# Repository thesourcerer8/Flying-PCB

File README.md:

# Flying-PCB
Quadcopter Project by MCI &amp; Infineon

This is a Quadcopter software and harddware design created as an cooperation by MCI and Infineon.

More information about the project: http://copter.rocks/

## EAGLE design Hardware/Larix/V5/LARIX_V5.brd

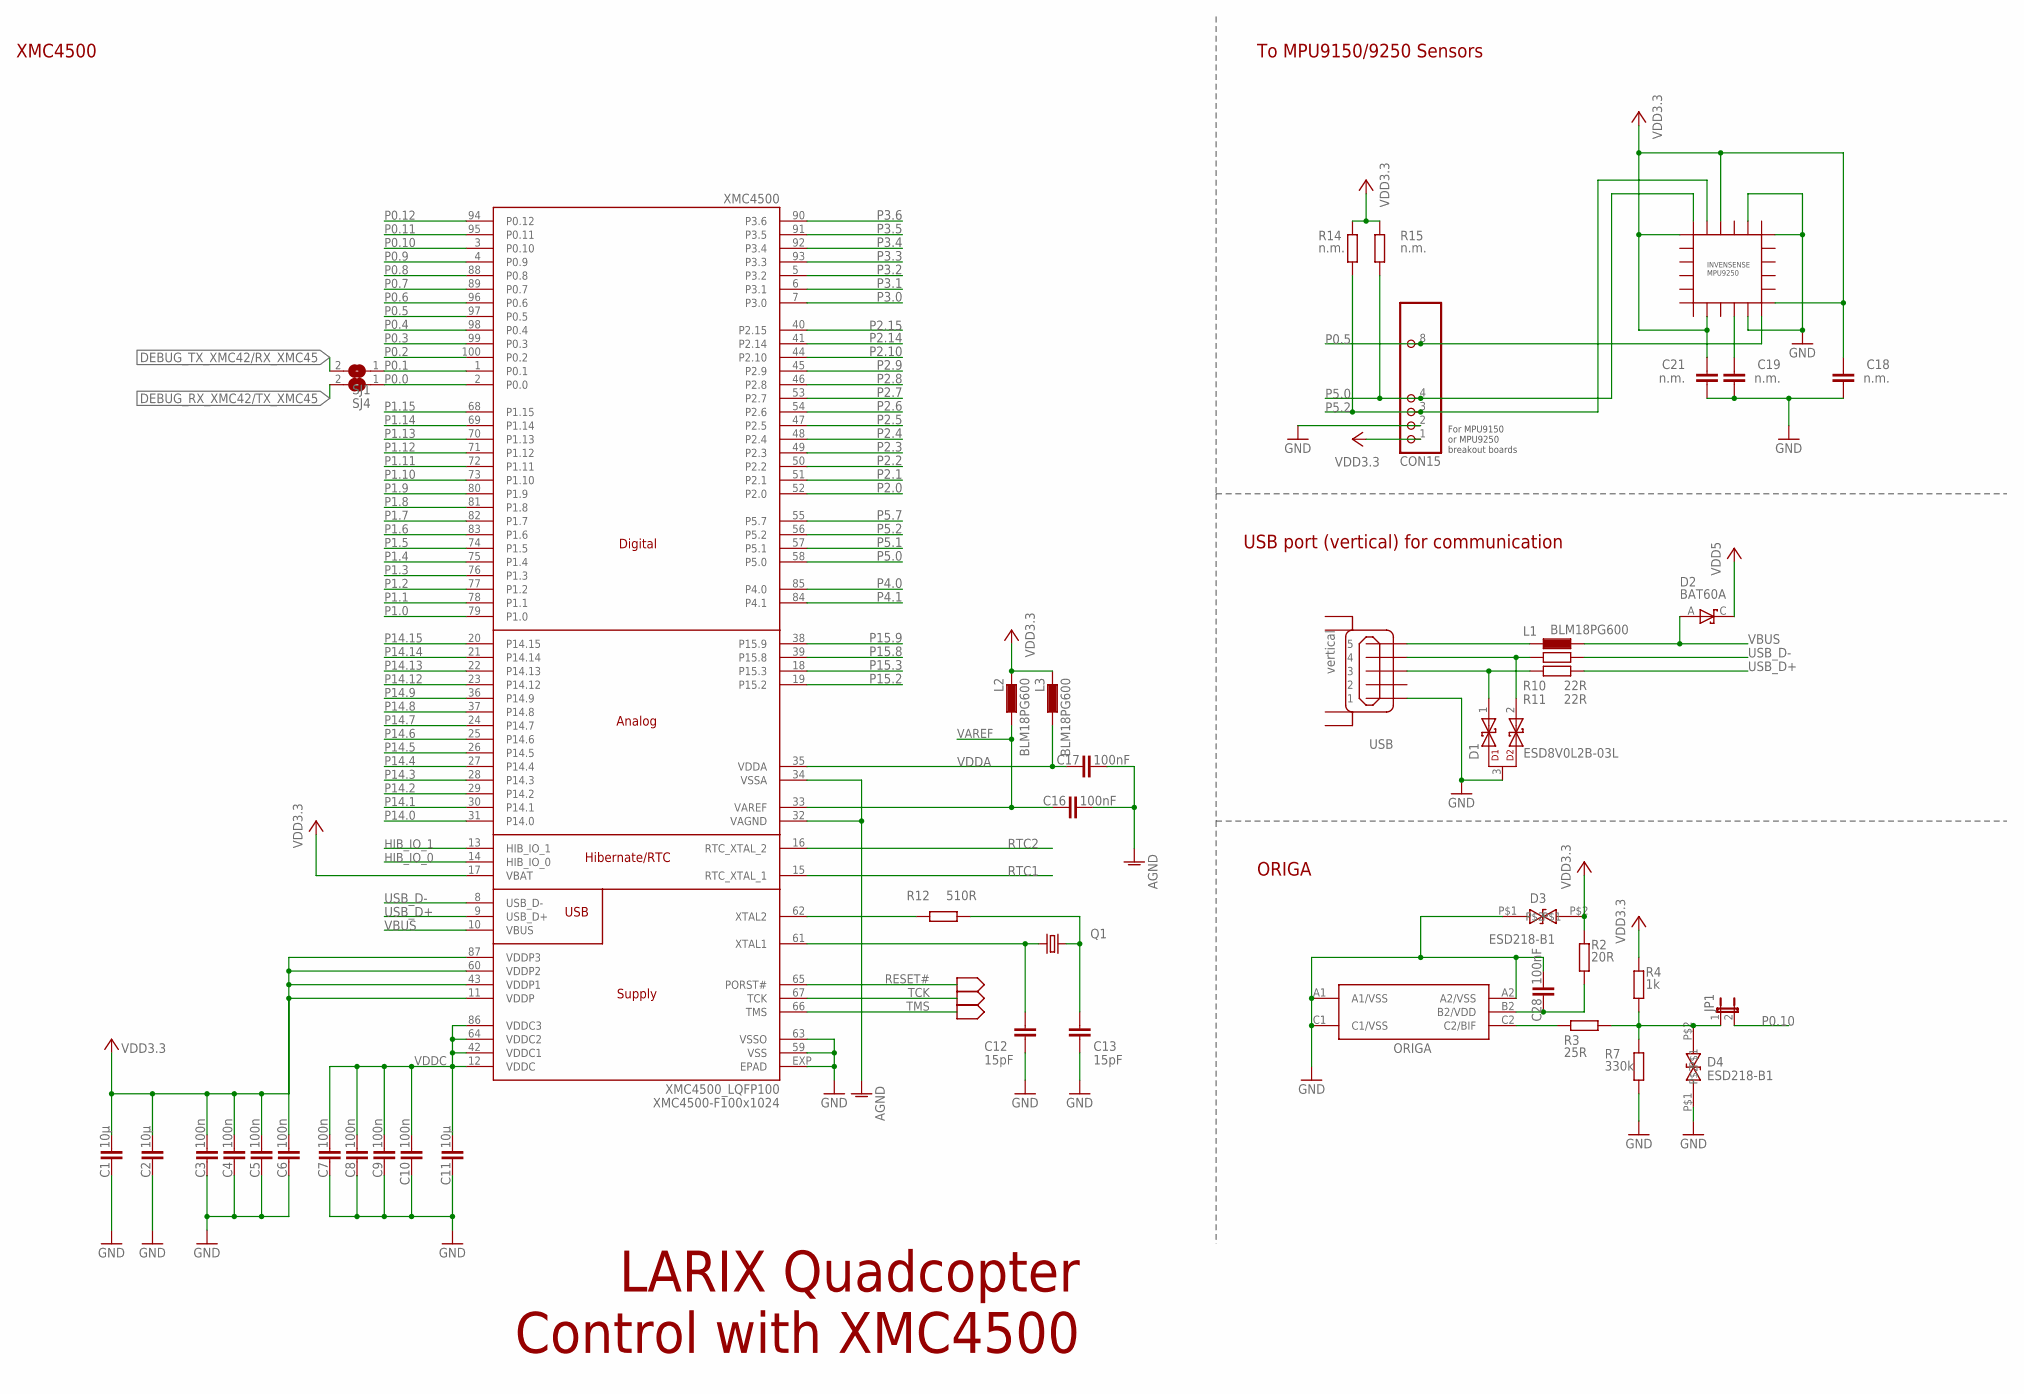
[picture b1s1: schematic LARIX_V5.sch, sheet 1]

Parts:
C1, C2, C11: 10µ; C0805K
C3, C4, C5, C6, C7, C8, C9, C10: 100n; C0603
C12, C13: 15pF; C0603
C16, C17, C28: 100nF; C0603
C18, C19, C21: n.m.; C0603
CON15: PINHD-1X10; 1X10
D1: ESD8V0L2B-03L; TSLP-3-1
D2: BAT60A; SOD323-R
D3, D4: ESD218-B1-02EL; TSLP-2-20
JP1: JP1E; JP1
L1, L2, L3: BLM18PG600; L1608
MPU9250: INVENSENSE9250EHERBY; QFN3X3-24+
ORIGA: ORIGA2L; WLB-5
Q1: 12MHZ/S/3.2X2.5; 32X25_4PAD
R2: 20R; R0603
R3: 25R; R0603
R4: 1k; R0603
R7: 330k; R0603
R10, R11: 22R; R0603
R12: 510R; R0603
R14, R15: n.m.; R0603
SJ1, SJ4: SJ
USB: vertical; USBVERTICAL
XMC4500: XMC4500_LQFP100; P/PG-LQFP-100-11

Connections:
AGND: C16.2, C17.2, XMC4500.32 (VAGND), XMC4500.34 (VSSA)
DEBUG_RX_XMC42/TX_XMC45: SJ4.2; also elsewhere on the board
DEBUG_TX_XMC42/RX_XMC45: SJ1.2; also elsewhere on the board
GND: C1.2, C2.2, C3.2, C4.2, C5.2, C6.2, C7.2, C8.2, C9.2, C10.2, C11.2, C12.2, C13.2, C18.1, C19.1, C21.1, C28.1, CON15.2, D1.3, D3.P$1, D4.P$1, MPU9250.11, MPU9250.18, MPU9250.20, ORIGA.A1 (A1/VSS), ORIGA.A2 (A2/VSS), ORIGA.C1 (C1/VSS), R7.2, USB.1, XMC4500.59 (VSS), XMC4500.63 (VSSO), XMC4500.EXP (EPAD); also elsewhere on the board
HIB_IO_0: XMC4500.14 (HIB_IO_0)
HIB_IO_1: XMC4500.13 (HIB_IO_1)
unnamed: C28.2, ORIGA.B2 (B2/VDD), R2.2
unnamed: R12.1, XMC4500.62 (XTAL2)
unnamed: C13.1, Q1.3 (2), R12.2
unnamed: C12.1, Q1.1, XMC4500.61 (XTAL1)
unnamed: D4.P$2, JP1.1, R3.2, R4.2, R7.1
unnamed: L1.2, USB.5
unnamed: ORIGA.C2 (C2/BIF), R3.1
unnamed: D1.2, R10.1, USB.4
unnamed: C19.2, MPU9250.10
unnamed: D1.1, R11.1, USB.3+ (3)
P0.0: SJ4.1, XMC4500.2 (P0.0); also elsewhere on the board
P0.1: SJ1.1, XMC4500.1 (P0.1); also elsewhere on the board
P0.2: XMC4500.100 (P0.2); also elsewhere on the board
P0.3: XMC4500.99 (P0.3); also elsewhere on the board
P0.4: XMC4500.98 (P0.4); also elsewhere on the board
P0.5: CON15.8, MPU9250.12, XMC4500.97 (P0.5)
P0.6: XMC4500.96 (P0.6)
P0.7: XMC4500.89 (P0.7); also elsewhere on the board
P0.8: XMC4500.88 (P0.8)
P0.9: XMC4500.4 (P0.9); also elsewhere on the board
P0.10: JP1.2, XMC4500.3 (P0.10)
P0.11: XMC4500.95 (P0.11)
P0.12: XMC4500.94 (P0.12)
P1.0: XMC4500.79 (P1.0); also elsewhere on the board
P1.1: XMC4500.78 (P1.1); also elsewhere on the board
P1.2: XMC4500.77 (P1.2); also elsewhere on the board
P1.3: XMC4500.76 (P1.3); also elsewhere on the board
P1.4: XMC4500.75 (P1.4)
P1.5: XMC4500.74 (P1.5); also elsewhere on the board
P1.6: XMC4500.83 (P1.6)
P1.7: XMC4500.82 (P1.7)
P1.8: XMC4500.81 (P1.8)
P1.9: XMC4500.80 (P1.9)
P1.10: XMC4500.73 (P1.10)
P1.11: XMC4500.72 (P1.11)
P1.12: XMC4500.71 (P1.12)
P1.13: XMC4500.70 (P1.13)
P1.14: XMC4500.69 (P1.14)
P1.15: XMC4500.68 (P1.15); also elsewhere on the board
P2.0: XMC4500.52 (P2.0)
P2.1: XMC4500.51 (P2.1); also elsewhere on the board
P2.2: XMC4500.50 (P2.2); also elsewhere on the board
P2.3: XMC4500.49 (P2.3); also elsewhere on the board
P2.4: XMC4500.48 (P2.4); also elsewhere on the board
P2.5: XMC4500.47 (P2.5); also elsewhere on the board
P2.6: XMC4500.54 (P2.6)
P2.7: XMC4500.53 (P2.7)
P2.8: XMC4500.46 (P2.8)
P2.9: XMC4500.45 (P2.9)
P2.10: XMC4500.44 (P2.10)
P2.14: XMC4500.41 (P2.14)
P2.15: XMC4500.40 (P2.15)
P3.0: XMC4500.7 (P3.0); also elsewhere on the board
P3.1: XMC4500.6 (P3.1); also elsewhere on the board
P3.2: XMC4500.5 (P3.2); also elsewhere on the board
P3.3: XMC4500.93 (P3.3)
P3.4: XMC4500.92 (P3.4)
P3.5: XMC4500.91 (P3.5); also elsewhere on the board
P3.6: XMC4500.90 (P3.6)
P4.0: XMC4500.85 (P4.0); also elsewhere on the board
P4.1: XMC4500.84 (P4.1)
P5.0: CON15.4, MPU9250.24, R15.1, XMC4500.58 (P5.0)
P5.1: XMC4500.57 (P5.1); also elsewhere on the board
P5.2: CON15.3, MPU9250.23, R14.1, XMC4500.56 (P5.2)
P5.7: XMC4500.55 (P5.7)
P14.0: XMC4500.31 (P14.0)
P14.1: XMC4500.30 (P14.1)
P14.2: XMC4500.29 (P14.2)
P14.3: XMC4500.28 (P14.3)
P14.4: XMC4500.27 (P14.4)
P14.5: XMC4500.26 (P14.5); also elsewhere on the board
P14.6: XMC4500.25 (P14.6)
P14.7: XMC4500.24 (P14.7); also elsewhere on the board
P14.8: XMC4500.37 (P14.8); also elsewhere on the board
P14.9: XMC4500.36 (P14.9)
P14.12: XMC4500.23 (P14.12)
P14.13: XMC4500.22 (P14.13)
P14.14: XMC4500.21 (P14.14)
P14.15: XMC4500.20 (P14.15)
P15.2: XMC4500.19 (P15.2)
P15.3: XMC4500.18 (P15.3)
P15.8: XMC4500.39 (P15.8)
P15.9: XMC4500.38 (P15.9)
RESET#: XMC4500.65 (PORST#); also elsewhere on the board
RTC1: XMC4500.15 (RTC_XTAL_1)
RTC2: XMC4500.16 (RTC_XTAL_2)
TCK: XMC4500.67 (TCK); also elsewhere on the board
TMS: XMC4500.66 (TMS); also elsewhere on the board
USB_D+: R11.2, XMC4500.9 (USB_D+)
USB_D-: R10.2, XMC4500.8 (USB_D-)
VAREF: C16.1, L2.1, XMC4500.33 (VAREF)
VBUS: D2.A, L1.1, XMC4500.10 (VBUS)
VDD3.3: C1.1, C2.1, C3.1, C4.1, C5.1, C6.1, C18.2, C21.2, CON15.1, D3.P$2, L2.2, L3.2, MPU9250.1, MPU9250.8, MPU9250.13, MPU9250.22, R2.1, R4.1, R14.2, R15.2, XMC4500.11 (VDDP), XMC4500.17 (VBAT), XMC4500.43 (VDDP1), XMC4500.60 (VDDP2), XMC4500.87 (VDDP3); also elsewhere on the board
VDD5: D2.C; also elsewhere on the board
VDDA: C17.1, L3.1, XMC4500.35 (VDDA)
VDDC: C7.1, C8.1, C9.1, C10.1, C11.1, XMC4500.12 (VDDC), XMC4500.42 (VDDC1), XMC4500.64 (VDDC2), XMC4500.86 (VDDC3)

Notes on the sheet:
LARIX Quadcopter Control with XMC4500
XMC4500-F100x1024
To MPU9150/9250 Sensors
ORIGA
XMC4500
For MPU9150 or MPU9250 breakout boards
USB port (vertical) for communication
ESD218-B1

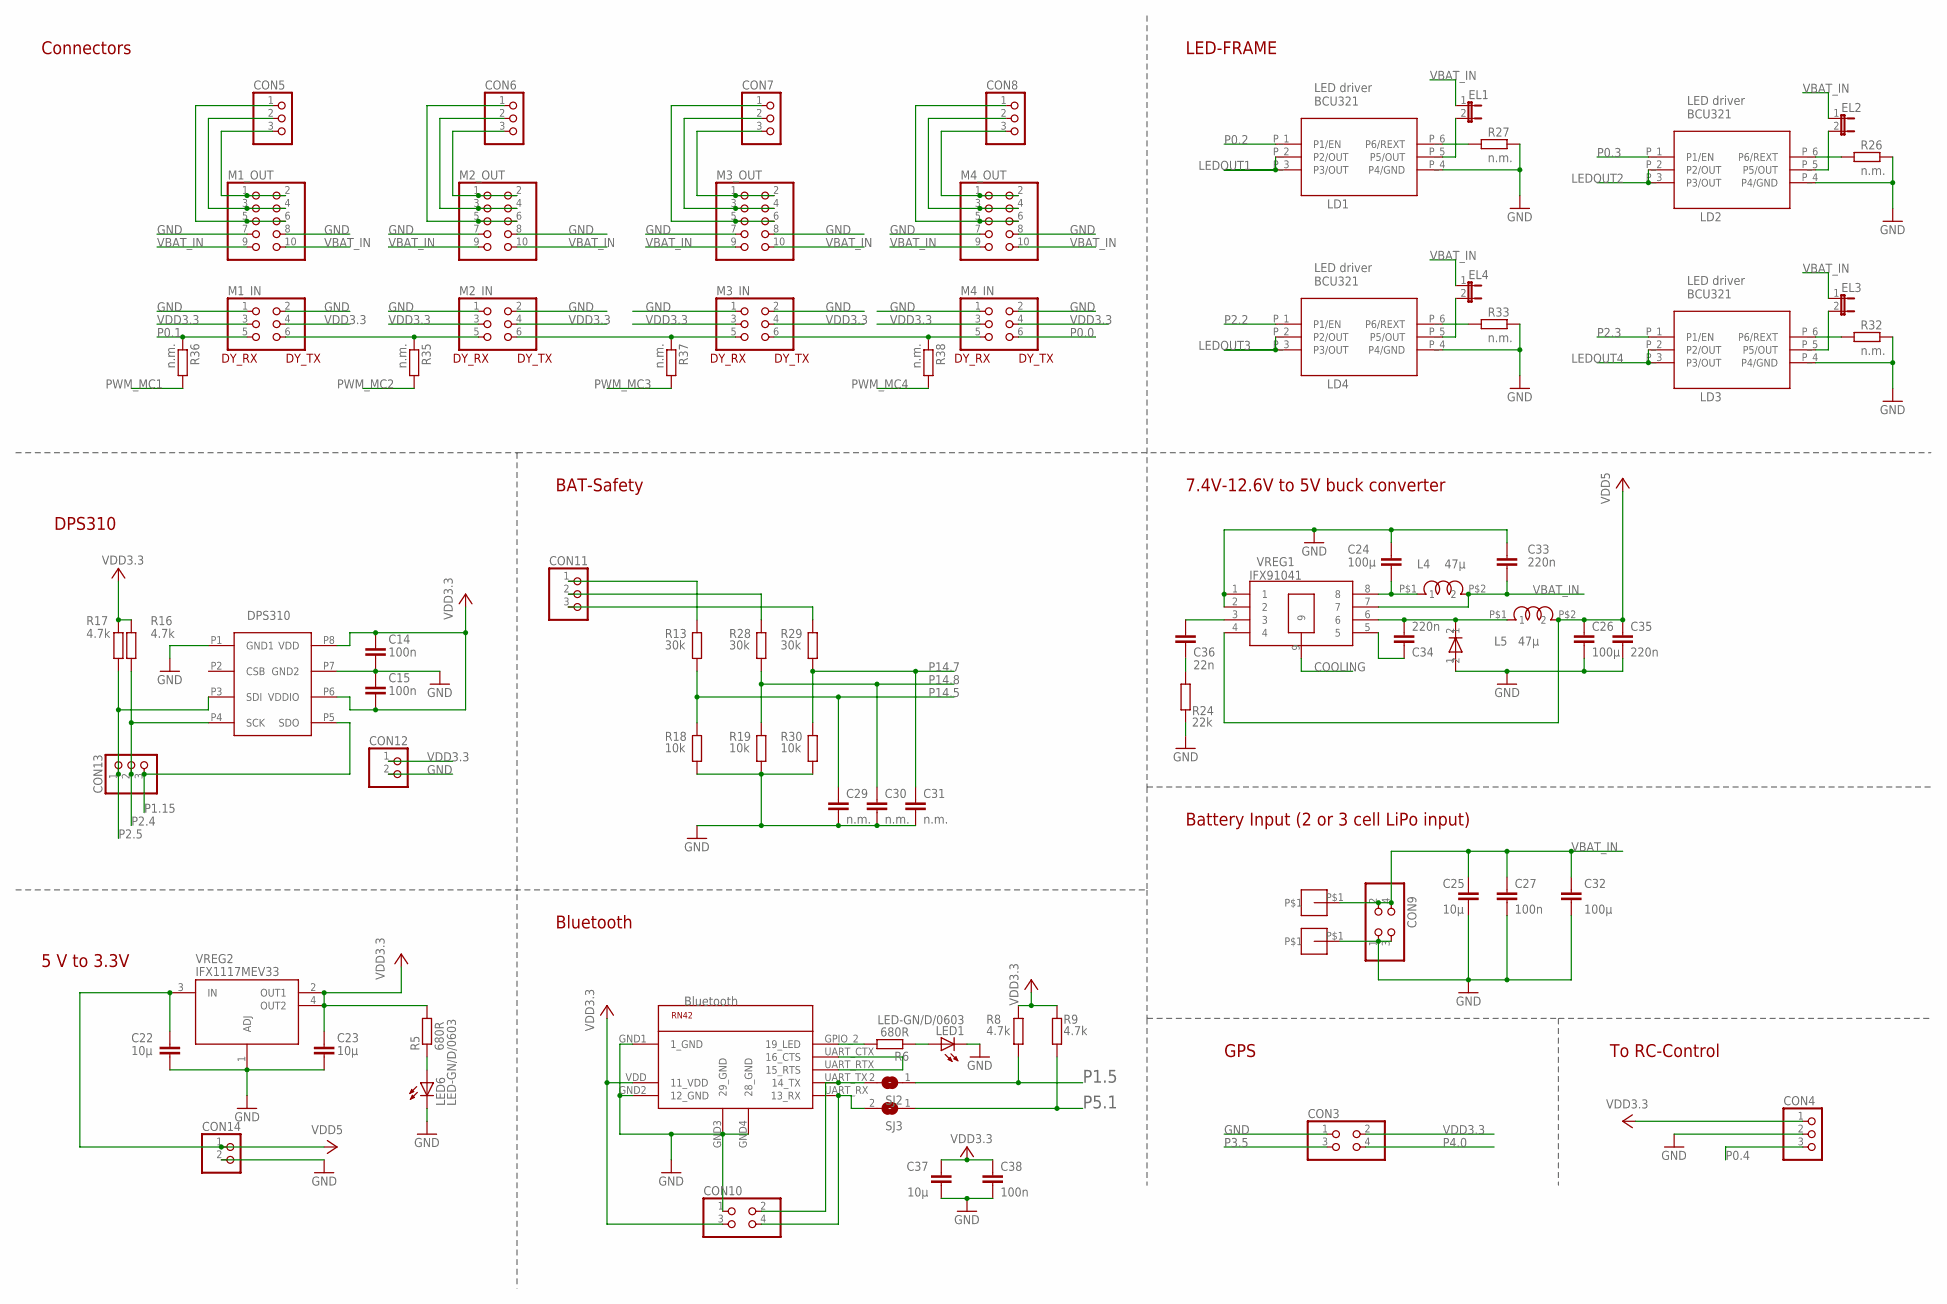
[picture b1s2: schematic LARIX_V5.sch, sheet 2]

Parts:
C14, C15, C27, C38: 100n; C0603
C22, C23, C25, C37: 10µ; C0805K
C24, C26, C32: 100µ; C1210
C29, C30, C31: n.m.; C0603
C33, C34, C35: 220n; C0603
C36: 22n; C0603
CON3, CON9, CON10: PINHD-2X2; 2X02
CON4, CON5, CON6, CON7, CON8, CON11, CON13: PINHD-1X3; 1X03
CON12, CON14: PINHD-1X2; 1X02
D6: BAS21-03W; INF-SOD323_V_1PRIMARY
DPS310: DPS310DRUCKSENSOR; LGA8R125P0X4_500X300X120
EL1, EL2, EL3, EL4: JP1E; JP1
L4, L5: 47µH; WE-TPC
LD1, LD2, LD3, LD4: BCU321; SC74
LED1, LED6: LED-GN/D/0603; CHIPLED_0603
M1_IN, M2_IN, M3_IN, M4_IN: PINHD-2X3; 2X03
M1_OUT, M2_OUT, M3_OUT, M4_OUT: PINHD-2X5; 2X05
PAD1, PAD2: PAD-BATTERY; BATT-SOLDER
R5, R6: 680R; R0603
R8, R9, R16, R17: 4.7k; R0603
R13, R28, R29: 30k; R0603
R18, R19, R30: 10k; R0603
R24: 22k; R0603
R26, R27, R32, R33, R35, R36, R37, R38: n.m.; R0603
RN42: BLUETOOTHRN42+SHIELD; RN42+SHIELD
SJ2, SJ3: SJ
VREG1: INF-PG-DSO-8-27_N_1; INF-PG-DSO-8-27_N_1PRIMARY
VREG2: IFX1117MEV33; SOT223

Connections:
COOLING: VREG1.9
GND: C14.2, C15.1, C22.2, C23.2, C24.1, C25.2, C26.2, C27.2, C29.2, C30.2, C31.2, C32.2, C33.1, C35.2, C37.2, C38.2, CON3.1, CON4.2, CON9.1, CON9.3, CON10.1, CON12.2, CON14.2, D6.1, DPS310.P1 (GND1), DPS310.P7 (GND2), LD1.P_4 (P4/GND), LD2.P_4 (P4/GND), LD3.P_4 (P4/GND), LD4.P_4 (P4/GND), LED1.C, LED6.C, M1_IN.1, M1_IN.2, M1_OUT.7, M1_OUT.8, M2_IN.1, M2_IN.2, M2_OUT.7, M2_OUT.8, M3_IN.1, M3_IN.2, M3_OUT.7, M3_OUT.8, M4_IN.1, M4_IN.2, M4_OUT.7, M4_OUT.8, PAD2.P$1, R18.2, R19.2, R24.2, R26.2, R27.2, R30.2, R32.2, R33.2, RN42.GND1 (1_GND), RN42.GND2 (12_GND), RN42.GND3 (29_GND), RN42.GND4 (28_GND), VREG1.1, VREG1.2, VREG2.1 (ADJ); also elsewhere on the board
LEDOUT1: EL1.2, LD1.P_2 (P2/OUT), LD1.P_3 (P3/OUT), LD1.P_5 (P5/OUT)
LEDOUT2: EL2.2, LD2.P_2 (P2/OUT), LD2.P_3 (P3/OUT), LD2.P_5 (P5/OUT)
LEDOUT3: EL4.2, LD4.P_2 (P2/OUT), LD4.P_3 (P3/OUT), LD4.P_5 (P5/OUT)
LEDOUT4: EL3.2, LD3.P_2 (P2/OUT), LD3.P_3 (P3/OUT), LD3.P_5 (P5/OUT)
unnamed: C36.1, VREG1.3
unnamed: CON5.1, M1_OUT.5, M1_OUT.6
unnamed: LED6.A, R5.1
unnamed: M2_IN.6, M3_IN.5, R37.1
unnamed: C36.2, R24.1
unnamed: LED1.A, R6.1
unnamed: CON5.2, M1_OUT.3, M1_OUT.4
unnamed: CON5.3, M1_OUT.1, M1_OUT.2
unnamed: R6.2, RN42.GPIO_2 (19_LED)
unnamed: RN42.UART_CTX (16_CTS), RN42.UART_RTX (15_RTS)
unnamed: C24.2, L4.P$1 (1), VREG1.8
unnamed: C34.1, D6.2, L5.P$1 (1), VREG1.6
unnamed: LD2.P_6 (P6/REXT), R26.1
unnamed: LD1.P_6 (P6/REXT), R27.1
unnamed: CON6.1, M2_OUT.5, M2_OUT.6
unnamed: CON11.1, R13.1
unnamed: CON6.3, M2_OUT.1, M2_OUT.2
unnamed: CON6.2, M2_OUT.3, M2_OUT.4
unnamed: CON11.2, R28.1
unnamed: CON8.1, M4_OUT.5, M4_OUT.6
unnamed: CON11.3, R29.1
unnamed: CON8.3, M4_OUT.1, M4_OUT.2
unnamed: CON8.2, M4_OUT.3, M4_OUT.4
unnamed: C34.2, VREG1.5
unnamed: CON7.1, M3_OUT.5, M3_OUT.6
unnamed: CON7.2, M3_OUT.3, M3_OUT.4
unnamed: CON7.3, M3_OUT.1, M3_OUT.2
unnamed: M3_IN.6, M4_IN.5, R38.1
unnamed: M1_IN.6, M2_IN.5, R35.1
unnamed: LD3.P_6 (P6/REXT), R32.1
unnamed: LD4.P_6 (P6/REXT), R33.1
P0.0: M4_IN.6; also elsewhere on the board
P0.1: M1_IN.5, R36.1; also elsewhere on the board
P0.2: LD1.P_1 (P1/EN); also elsewhere on the board
P0.3: LD2.P_1 (P1/EN); also elsewhere on the board
P0.4: CON4.3; also elsewhere on the board
P1.5: R8.2, SJ2.1; also elsewhere on the board
P1.5S: CON10.2, RN42.UART_TX (14_TX), SJ2.2
P1.15: CON13.3, DPS310.P5 (SDO); also elsewhere on the board
P2.2: LD4.P_1 (P1/EN); also elsewhere on the board
P2.3: LD3.P_1 (P1/EN); also elsewhere on the board
P2.4: CON13.2, DPS310.P4 (SCK), R16.2; also elsewhere on the board
P2.5: CON13.1, DPS310.P3 (SDI), R17.2; also elsewhere on the board
P3.5: CON3.3; also elsewhere on the board
P4.0: CON3.4; also elsewhere on the board
P5.1: R9.2, SJ3.1; also elsewhere on the board
P5.1S: CON10.4, RN42.UART_RX (13_RX), SJ3.2
P14.5: C29.1, R13.2, R18.1; also elsewhere on the board
P14.7: C31.1, R29.2, R30.1; also elsewhere on the board
P14.8: C30.1, R19.1, R28.2; also elsewhere on the board
PWM_MC1: R36.2; also elsewhere on the board
PWM_MC2: R35.2; also elsewhere on the board
PWM_MC3: R37.2; also elsewhere on the board
PWM_MC4: R38.2; also elsewhere on the board
VBAT_IN: C25.1, C27.1, C32.1, C33.2, CON9.2, CON9.4, EL1.1, EL2.1, EL3.1, EL4.1, L4.P$2 (2), M1_OUT.9, M1_OUT.10, M2_OUT.9, M2_OUT.10, M3_OUT.9, M3_OUT.10, M4_OUT.9, M4_OUT.10, PAD1.P$1, VREG1.7
VDD3.3: C14.1, C15.2, C23.1, C37.1, C38.1, CON3.2, CON4.1, CON10.3, CON12.1, DPS310.P6 (VDDIO), DPS310.P8 (VDD), M1_IN.3, M1_IN.4, M2_IN.3, M2_IN.4, M3_IN.3, M3_IN.4, M4_IN.3, M4_IN.4, R5.2, R8.1, R9.1, R16.1, R17.1, RN42.VDD (11_VDD), VREG2.2 (OUT1), VREG2.4 (OUT2); also elsewhere on the board
VDD5: C22.1, C26.1, C35.1, CON14.1, L5.P$2 (2), VREG1.4, VREG2.3 (IN); also elsewhere on the board

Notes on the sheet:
Connectors
DY_RX
DY_TX
LED-FRAME
LED driver BCU321
LD1
LD2
LD4
LD3
GPS
To RC-Control
DPS310
5 V to 3.3V
7.4V-12.6V to 5V buck converter
Bluetooth
BAT-Safety
Battery Input (2 or 3 cell LiPo input)
L4 47µ
L5 47µ
VREG1 IFX91041

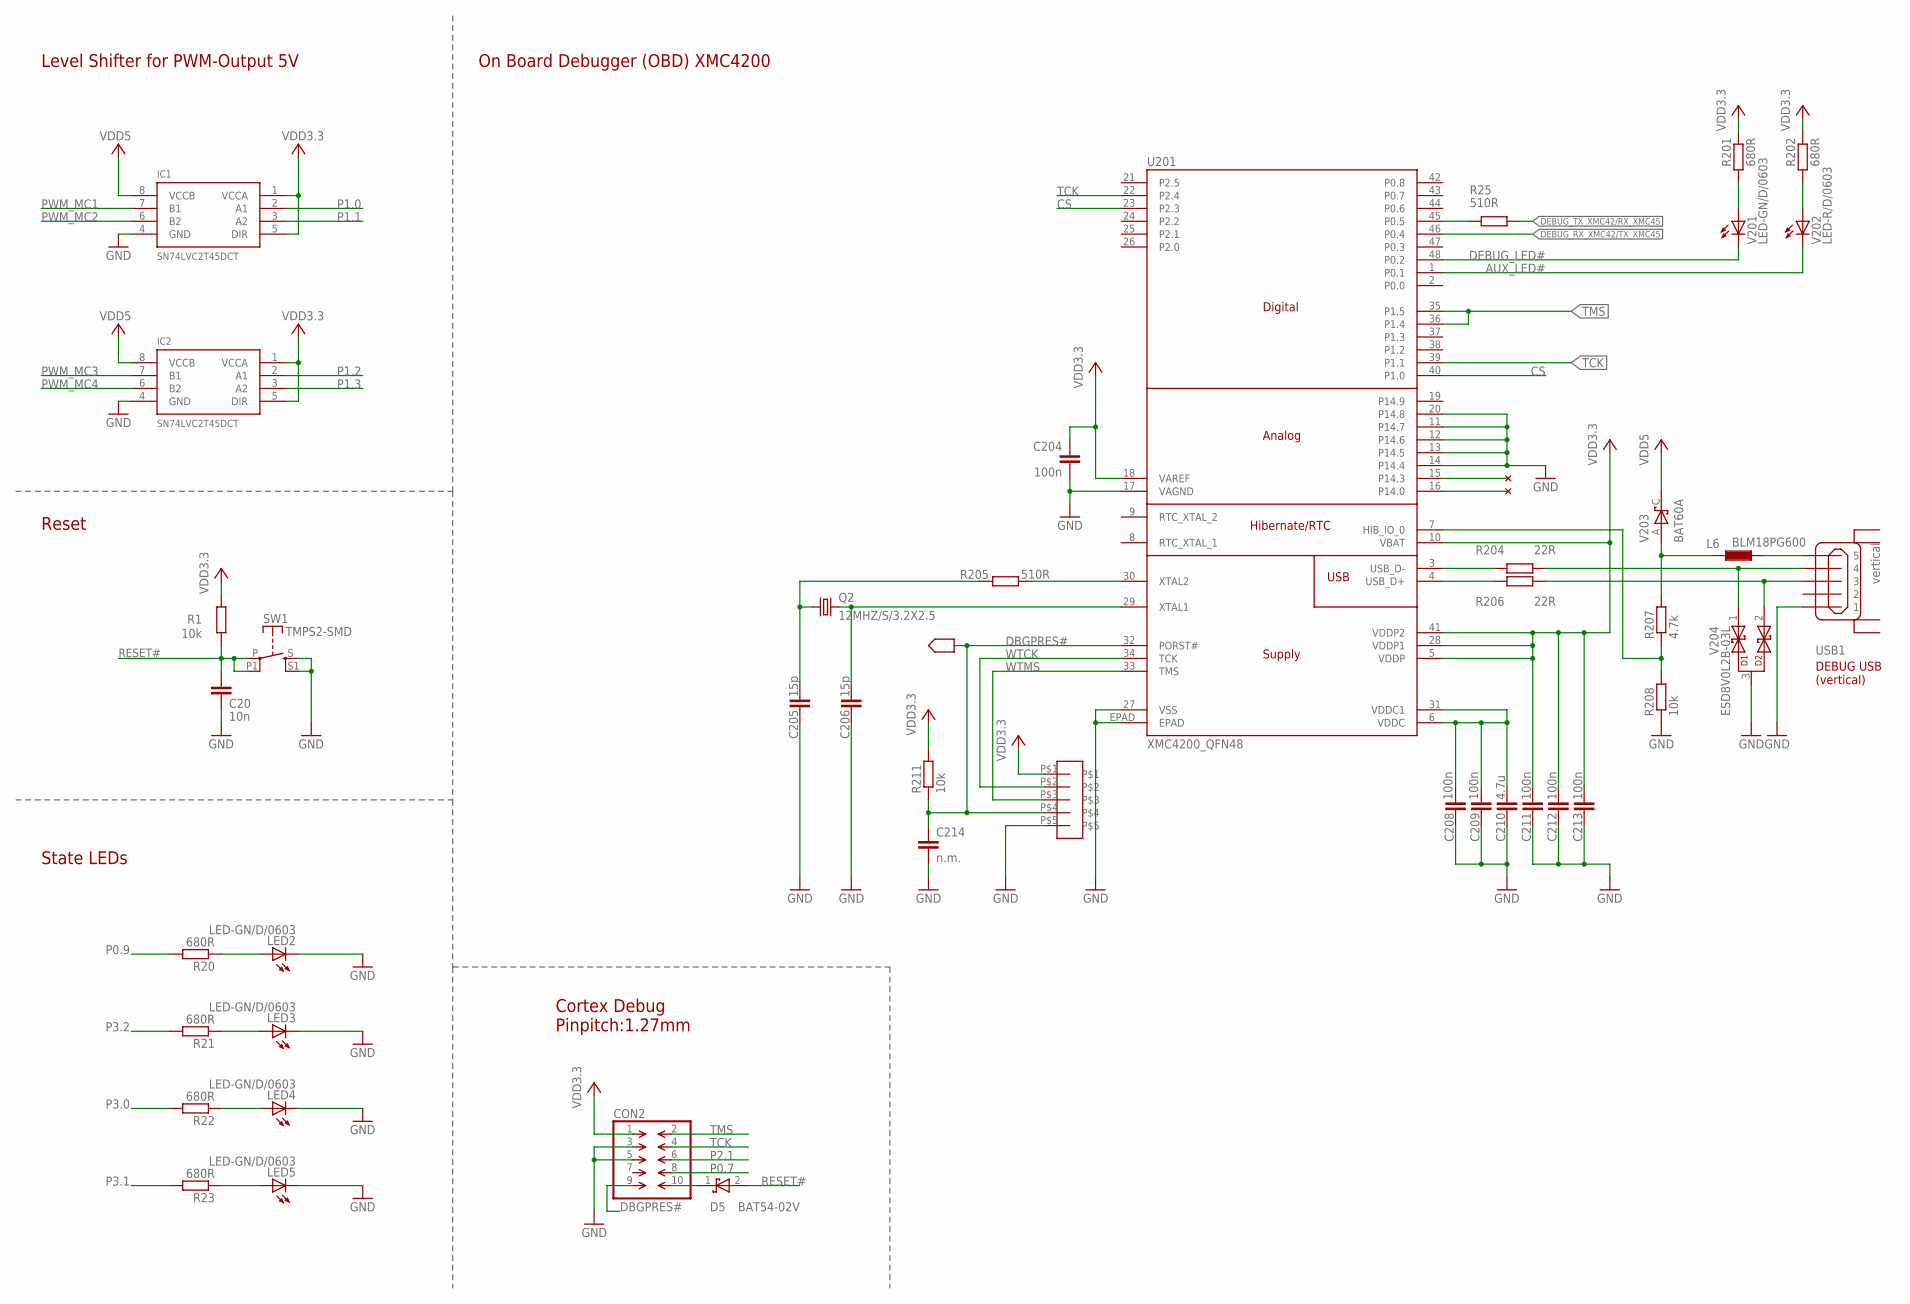
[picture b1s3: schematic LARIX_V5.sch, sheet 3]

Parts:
C20: 10n; C0603
C204, C208, C209, C211, C212, C213: 100n; C0402
C205, C206: 15p; C0402
C210: 4.7u; C0805K
C214: n.m.; C0402
CON2: FTSH-105-01-F-D-K
D5: BAT54-02V; SC79
IC1, IC2: SN74LVC2T45DCT; DCT_R-PDSO-G8
L6: BLM18PG600; L1608
LED2, LED3, LED4, LED5: LED-GN/D/0603; CHIPLED_0603
Q2: 12MHZ/S/3.2X2.5; 32X25_4PAD
R1: 10k; R0603
R20, R21, R22, R23, R201, R202: 680R; R0603
R25: 510R; R0402
R204, R206: 22R; R0402
R205: 510R; R0603
R207: 4.7k; R0402
R208, R211: 10k; R0402
SW1: TMPS2-SMD; FSM2JSMA
U201: XMC4200_QFN48; QFN-48-7X7
U$9: 127MARKED; PINHEAD_127
U$11: SEGGER.L_100; LOGO_100
USB1: vertical; USBVERTICAL
V201: LED-GN/D/0603; CHIPLED_0603
V202: LED-R/D/0603; CHIPLED_0603
V203: BAT60A; SOD323-R
V204: ESD8V0L2B-03L; TSLP-3-1

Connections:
AUX_LED#: U201.1 (P0.1), V202.C
CS: U201.23 (P2.3), U201.40 (P1.0)
DBGPRES#: C214.1, CON2.9, R211.1, U201.32 (PORST#), U$9.P$4
DEBUG_LED#: U201.48 (P0.2), V201.C
DEBUG_RX_XMC42/TX_XMC45: U201.46 (P0.4); also elsewhere on the board
DEBUG_TX_XMC42/RX_XMC45: R25.2; also elsewhere on the board
GND: C20.2, C204.2, C205.2, C206.2, C208.2, C209.2, C210.2, C211.2, C212.2, C213.2, C214.2, CON2.3, CON2.5, IC1.4 (GND), IC2.4 (GND), LED2.C, LED3.C, LED4.C, LED5.C, R208.1, SW1.S, SW1.S1 (S), U201.11 (P14.7), U201.12 (P14.6), U201.13 (P14.5), U201.14 (P14.4), U201.17 (VAGND), U201.20 (P14.8), U201.27 (VSS), U201.EPAD, U$9.P$5, USB1.1, V204.3; also elsewhere on the board
unnamed: LED2.A, R20.1
unnamed: LED3.A, R21.1
unnamed: R204.2, USB1.4, V204.1
unnamed: CON2.10, D5.1 (C)
unnamed: LED4.A, R22.1
unnamed: LED5.A, R23.1
unnamed: R206.2, USB1.3+ (3), V204.2
unnamed: C205.1, Q2.1, R205.2
unnamed: R205.1, U201.30 (XTAL2)
unnamed: L6.2, R207.2, V203.A
unnamed: C206.1, Q2.3 (2), U201.29 (XTAL1)
unnamed: R201.2, V201.A
unnamed: R25.1, U201.45 (P0.5)
unnamed: R207.1, R208.2, U201.7 (HIB_IO_0)
unnamed: R202.2, V202.A
P0.7: CON2.8; also elsewhere on the board
P0.9: R20.2; also elsewhere on the board
P1.0: IC1.2 (A1); also elsewhere on the board
P1.1: IC1.3 (A2); also elsewhere on the board
P1.2: IC2.2 (A1); also elsewhere on the board
P1.3: IC2.3 (A2); also elsewhere on the board
P2.1: CON2.6; also elsewhere on the board
P3.0: R22.2; also elsewhere on the board
P3.1: R23.2; also elsewhere on the board
P3.2: R21.2; also elsewhere on the board
PWM_MC1: IC1.7 (B1); also elsewhere on the board
PWM_MC2: IC1.6 (B2); also elsewhere on the board
PWM_MC3: IC2.7 (B1); also elsewhere on the board
PWM_MC4: IC2.6 (B2); also elsewhere on the board
RESET#: C20.1, D5.2 (A), R1.1, SW1.P, SW1.P1; also elsewhere on the board
TCK: CON2.4, U201.22 (P2.4), U201.39 (P1.1); also elsewhere on the board
TMS: CON2.2, U201.35 (P1.5), U201.36 (P1.4); also elsewhere on the board
USBVCC: L6.1, USB1.5
VDD3.3: C204.1, C211.1, C212.1, C213.1, CON2.1, IC1.1 (VCCA), IC1.5 (DIR), IC2.1 (VCCA), IC2.5 (DIR), R1.2, R201.1, R202.1, R211.2, U201.5 (VDDP), U201.10 (VBAT), U201.18 (VAREF), U201.28 (VDDP1), U201.41 (VDDP2), U$9.P$1; also elsewhere on the board
VDD5: IC1.8 (VCCB), IC2.8 (VCCB), V203.C; also elsewhere on the board
WTCK: U201.34 (TCK), U$9.P$2
WTMS: U201.33 (TMS), U$9.P$3
WUSB_DM: R204.1, U201.3 (USB_D-)
WUSB_DP: R206.1, U201.4 (USB_D+)
WVDDC: C208.1, C209.1, C210.1, U201.6 (VDDC), U201.31 (VDDC1)

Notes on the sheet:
State LEDs
Reset
Level Shifter for PWM-Output 5V
DEBUG USB (vertical)
Cortex Debug Pinpitch:1.27mm
On Board Debugger (OBD) XMC4200

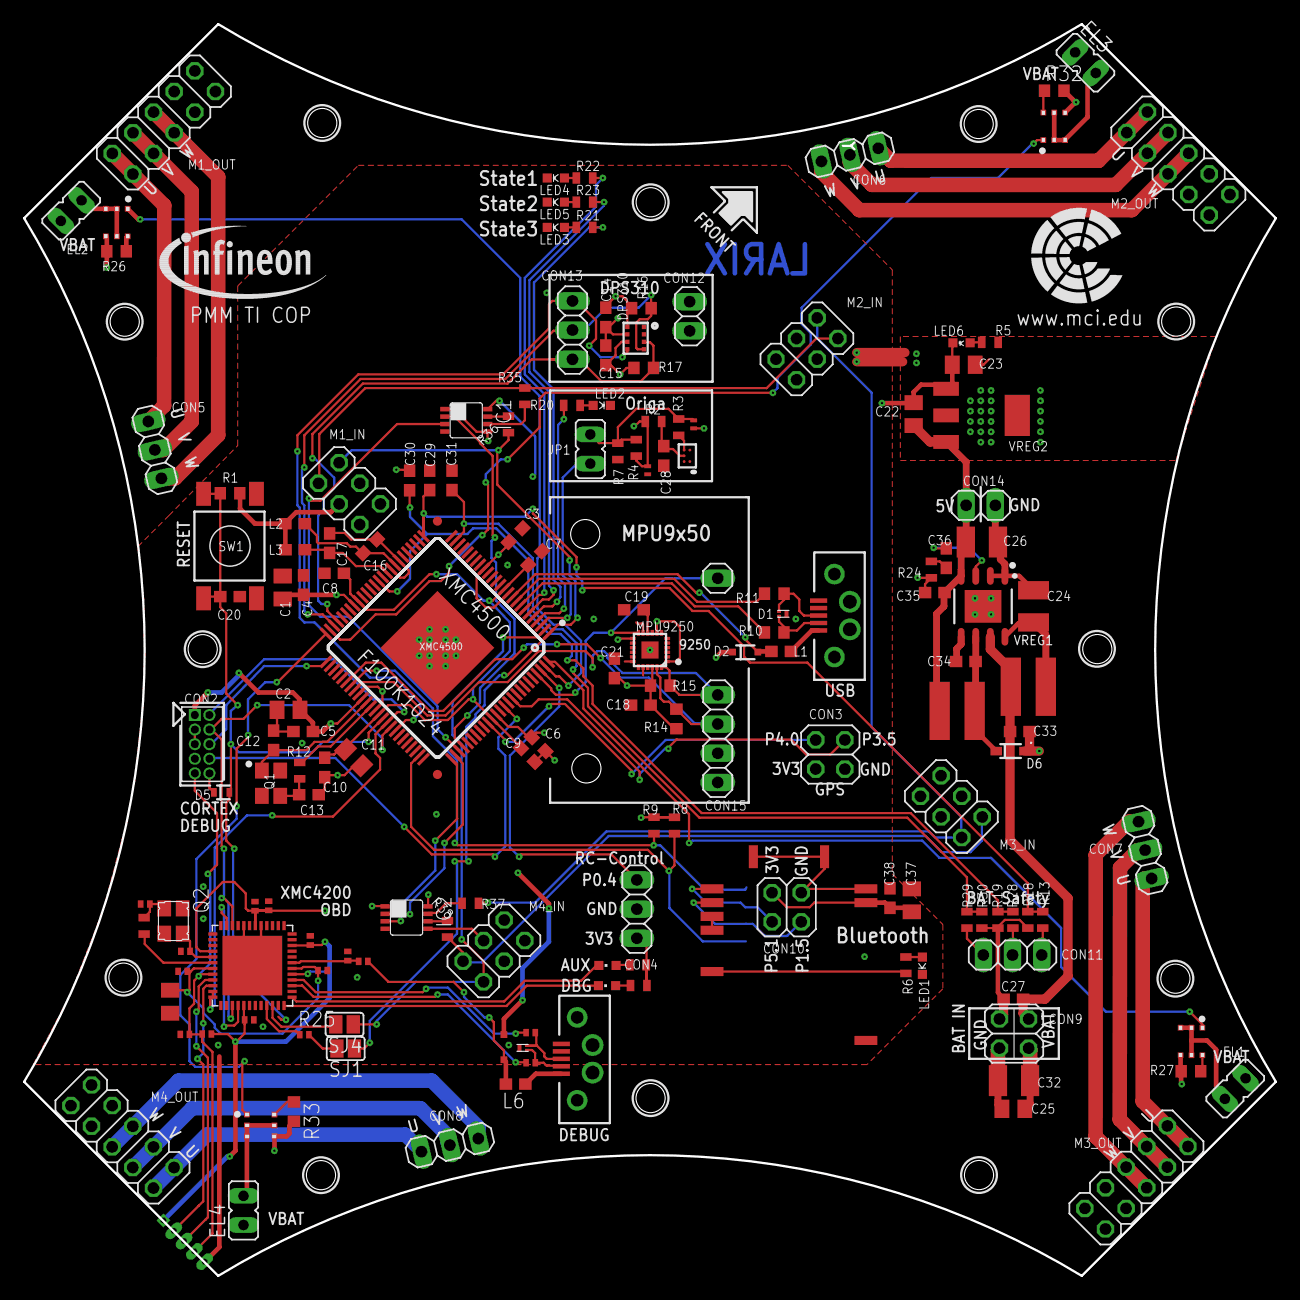
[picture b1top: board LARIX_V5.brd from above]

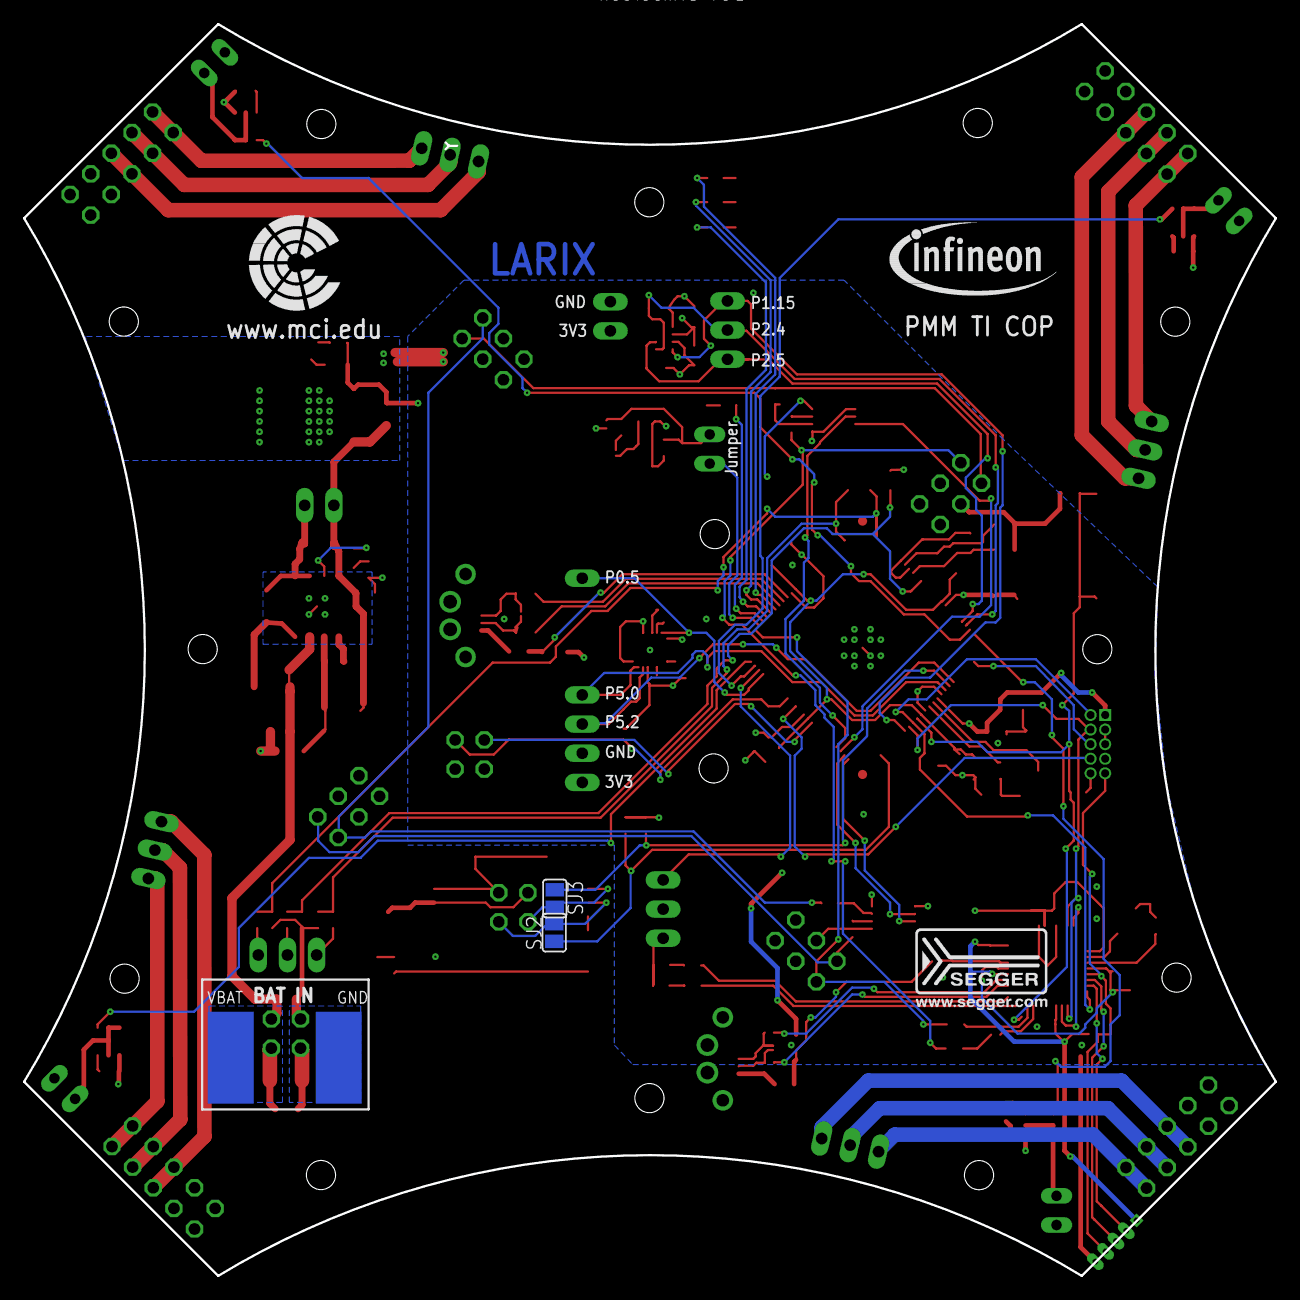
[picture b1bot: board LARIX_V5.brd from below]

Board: 4 copper layers, 109.0 x 109.0 mm, 168 parts (4 on the bottom side), 123 nets.
